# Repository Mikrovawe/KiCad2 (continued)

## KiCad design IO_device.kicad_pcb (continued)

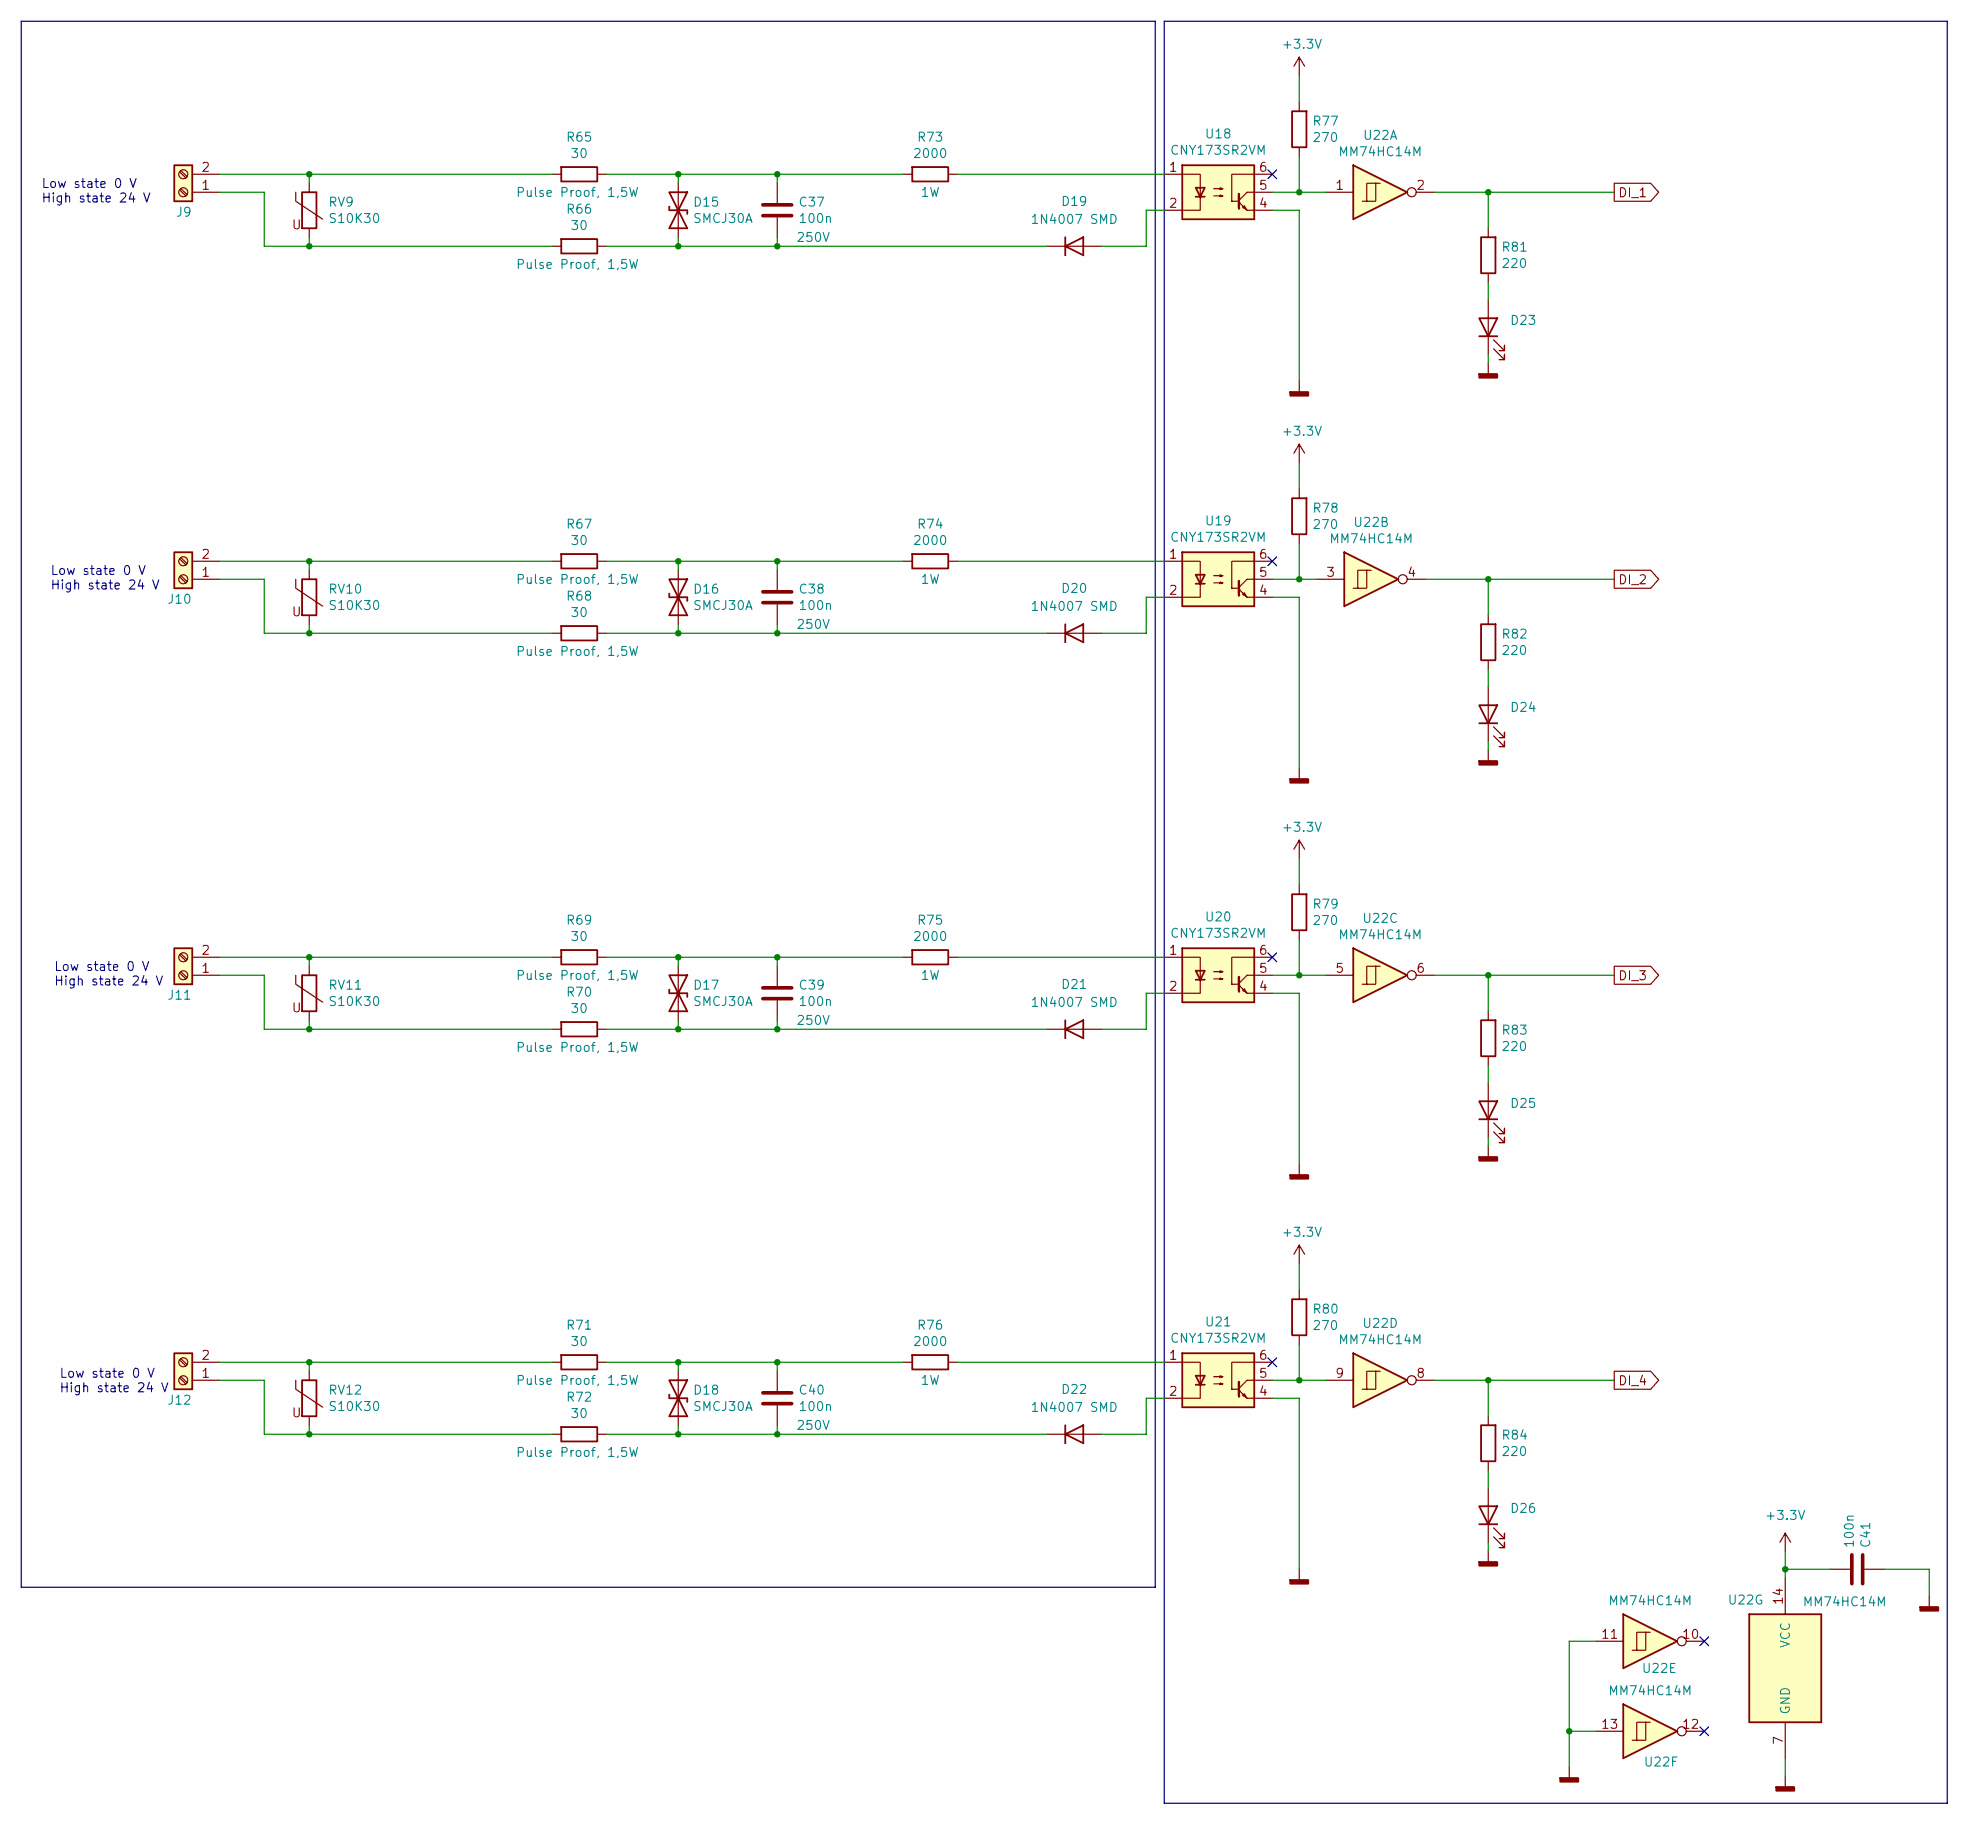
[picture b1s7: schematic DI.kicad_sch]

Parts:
C37, C38, C39, C40: 100n; C_1206_3216Metric; Voltage 250V
C41: 100n; C_1206_3216Metric
D15, D16, D17, D18: SMCJ30A; D_SMC
D19, D20, D21, D22: 1N4007 SMD; D_SOD-123
D23, D24, D25, D26: Green LED 3mm; D_1206_3216Metric
J9, J10, J11, J12: Screw_Terminal_01x02; TerminalBlock_Phoenix_MKDS-3-2-5.08_1x02_P5.08mm_Horizontal
R65, R66, R67, R68, R69, R70, R71, R72: 30; R_2512_6332Metric; Voltage Pulse Proof, 1,5W
R73, R74, R75, R76: 2000; R_2512_6332Metric
R77, R78, R79, R80: 270; R_1206_3216Metric
R81, R82, R83, R84: 220; R_1206_3216Metric
RV9, RV10, RV11, RV12: S10K30; RV_Disc_D12mm_W5.1mm_P7.5mm
U18, U19, U20, U21: CNY173SR2VM; DIP-6_W7.62mm_SMDSocket_SmallPads
U22: MM74HC14M; SOIC-14_3.9x8.7mm_P1.27mm

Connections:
+3.3V: C41.2, R77.2, R78.2, R79.2, R80.2, U22.14 (VCC); also elsewhere on the board
DI_1: R81.2, U22.2; also elsewhere on the board
DI_2: R82.2, U22.4; also elsewhere on the board
DI_3: R83.2, U22.6; also elsewhere on the board
DI_4: R84.2, U22.8; also elsewhere on the board
GNDD: C41.1, D23.1 (K), D24.1 (K), D25.1 (K), D26.1 (K), U18.4, U19.4, U20.4, U21.4, U22.7 (GND), U22.11, U22.13; also elsewhere on the board
unnamed: C37.1, D15.1 (A1), R65.1, R73.2
unnamed: C37.2, D15.2 (A2), D19.1 (K), R66.1
unnamed: C38.1, D16.1 (A1), R67.1, R74.2
unnamed: C38.2, D16.2 (A2), D20.1 (K), R68.1
unnamed: C39.1, D17.1 (A1), R69.1, R75.2
unnamed: C39.2, D17.2 (A2), D21.1 (K), R70.1
unnamed: C40.1, D18.1 (A1), R71.1, R76.2
unnamed: C40.2, D18.2 (A2), D22.1 (K), R72.1
unnamed: D19.2 (A), U18.2
unnamed: D20.2 (A), U19.2
unnamed: D21.2 (A), U20.2
unnamed: D22.2 (A), U21.2
unnamed: D23.2 (A), R81.1
unnamed: D24.2 (A), R82.1
unnamed: D25.2 (A), R83.1
unnamed: D26.2 (A), R84.1
unnamed: J9.1, R66.2, RV9.2
unnamed: J9.2, R65.2, RV9.1
unnamed: J10.1, R68.2, RV10.2
unnamed: J10.2, R67.2, RV10.1
unnamed: J11.1, R70.2, RV11.2
unnamed: J11.2, R69.2, RV11.1
unnamed: J12.1, R72.2, RV12.2
unnamed: J12.2, R71.2, RV12.1
unnamed: R73.1, U18.1
unnamed: R74.1, U19.1
unnamed: R75.1, U20.1
unnamed: R76.1, U21.1
unnamed: R77.1, U18.5, U22.1
unnamed: R78.1, U19.5, U22.3
unnamed: R79.1, U20.5, U22.5
unnamed: R80.1, U21.5, U22.9

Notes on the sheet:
Low state 0 V High state 24 V

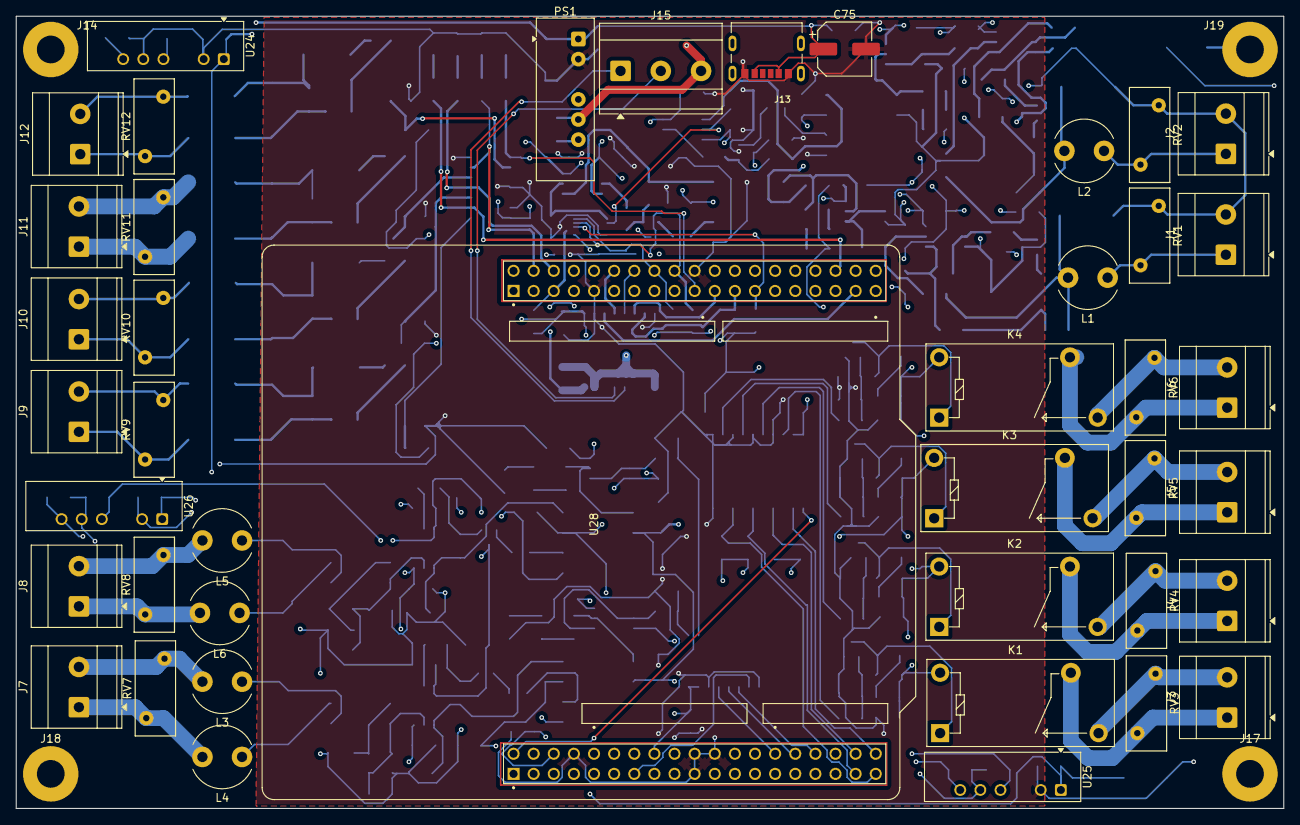
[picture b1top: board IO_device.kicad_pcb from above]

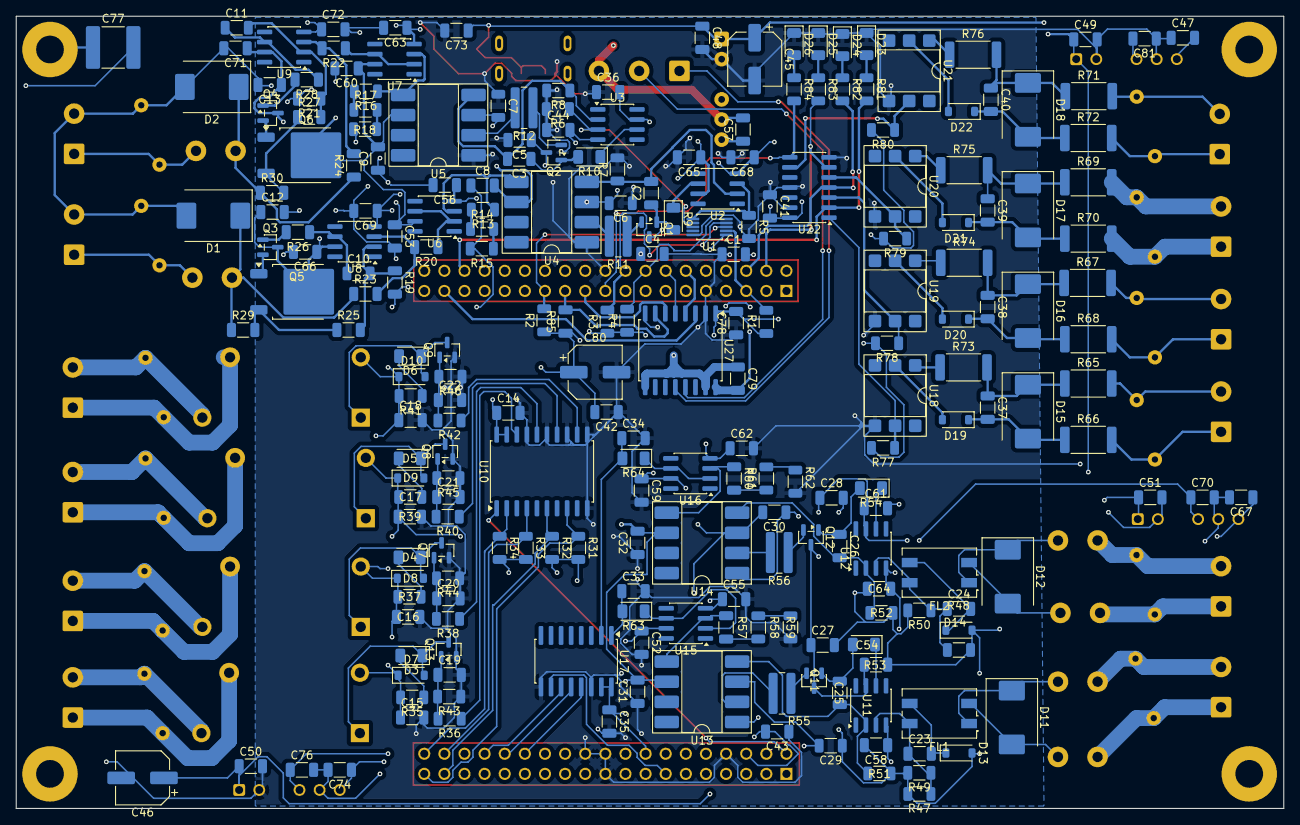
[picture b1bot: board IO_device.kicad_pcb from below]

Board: 4 copper layers, 160.0 x 100.0 mm, 274 parts (228 on the bottom side), 162 nets.

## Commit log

2026-02-03 IO and AO added in functional blocks
2026-02-04 alueet laatikoitu, ensimmäiset input osat laitettu
2026-02-05 Janin templaten mukainen
2026-02-08 missing AO and power
2026-02-09 all components in place
2026-02-09 some of wiring done
2026-02-11 removed unnecessary files and added them to gitignore
2026-02-11 wiring part 2
2026-02-15 started wiring
2026-02-17 readme edit
2026-03-07 all routed, no errors, missing copper
2026-03-13 copper done
